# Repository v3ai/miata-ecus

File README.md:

# miata-ecus

A plug-in [rusEFI](https://rusefi.com) engine computer for the 1989–2005 Mazda Miata (NA and NB). It has two parts:

- **One universal daughterboard.** It does all the engine control: an STM32F405 (an STM32F407 up to rev 0.11) running rusEFI, plus an on-board
  LSU 4.9 wideband controller (the open-source FOME/rusEFI design).
- **A motherboard for each model year.** Each one takes the stock harness connector and carries the year-specific
  wiring, the MAP sensor, the wideband sensor plug, the add-on header and USB-C. It goes in the stock ECU's case
  (1990–95; the 1996–2005 fit is unchecked) with three openings cut: the wideband plug, USB-C and the MAP hose.

The daughterboard is a castellated module: it lies flat on the motherboard, its 80 edge pins soldered to two rows of lands.

<table>
<tr>
<td width="50%"></td>
<td width="50%"></td>
</tr>
<tr>
<td align="center"><sub>Daughterboard lifted off its lands</sub></td>
<td align="center"><sub>The universal daughterboard (rev 0.14)</sub></td>
</tr>
</table>

<sub>Renders from the 3D viewer in <a href="viewer/"><code>viewer/</code></a>, with black solder mask (<code>MASK=black</code> in <code>viewer/pcb3d.py</code>). The harness header, the wideband connector, the card socket, the MAP sensor and the heater fuse F1 are simplified stand-in models.</sub>

**Who it is for:** people who want to replace the stock engine computer of a manual-gearbox Miata with a tunable,
open-source one, and can do their own wiring and tuning. It is for off-road and competition use. Automatic cars are untested.

## Start here: pick your year

One page per model-year range, with what to add, where the stock ECU is, the steps in order, the settings and the
first-start checks:

[**1989–93**](quickstart/1989-93.md) · [**1994–95**](quickstart/1994-95.md) · [**1996–97**](quickstart/1996-97.md) ·
[**1999–2000**](quickstart/1999-2000.md) · [**2001–05**](quickstart/2001-05.md)

**Status:** no board has been built or run yet. Every board is fully routed and passes KiCad DRC, and the designs have
been checked on the desk and in simulation ([VERIFICATION.md](VERIFICATION.md)), but no person has reviewed the
schematics. The supported path is an assembled unit until a first board has been built.

| If you want to | Read |
|---|---|
| Build the boards yourself (solder the module, first flash, bench check) | [BUILD.md](BUILD.md) |
| Fit the ECU to a car (labelled pictures, pin maps, MAP hose, wideband, first start) | [INSTALL.md](INSTALL.md) |
| Order the boards and parts | [ORDERING.md](ORDERING.md) |
| See what changed in each revision | [CHANGES.md](CHANGES.md) |

What changed in each revision: [CHANGES.md](CHANGES.md)

## Features and limitations

No board has been built yet. "Can" below means the hardware is designed for it and the firmware is set up for it; where
the firmware part has run in [emulation](firmware/sim/), that is as far as the proof goes.

### What it can do

**On every year**
- **Plugs into the stock harness** and goes in the stock ECU's case (1990–95; the 1996–2005 fit is unchecked) with
  three openings cut.
- **Fuel from manifold pressure** (speed-density), with the MAP sensor on the board. The ECU ignores the stock
  airflow meter's signal.
- **Reads the car's own air-temperature sensor**, with nothing to wire: on 1990–97 it is inside the airflow meter, so
  the meter stays plugged in; on 1999–2005 it is the sensor in the air filter box. Taking the meter out is an option
  with a GM sensor ([INSTALL.md](INSTALL.md#taking-the-airflow-meter-out-optional)).
- **MAP sensor good for boost:** 15–700 kPa absolute, so a turbo or supercharger needs no sensor change.
- **Wideband oxygen sensor controller on the board** for a Bosch LSU 4.9. No separate gauge or controller box. The
  board's connector takes AEM's ready-made X-Series sensor harness (30-3427).
- **Closed-loop fuel from the wideband**, switched on from the first start: ±10 % at idle and cruise, +10 / −5 %
  under load.
- **A base tune for each year**, loaded by the year button in TunerStudio ([what is in it](firmware/README.md#base-tune)).
- **Four injector outputs** for high-impedance injectors. Sequential on 1994–2005; in pairs on 1989–93, as the
  stock harness is wired (two jumpers on that board are for a car with one wire per injector).
- **Four ignition outputs** (5 V logic): two on the harness for the stock coils, two more on the AUX header for one
  coil per cylinder.
- **Closed-loop idle** (on cars with a throttle position sensor), radiator fan, second fan, A/C clutch, fuel pump,
  check-engine light and tachometer, on the stock wires.
- **One USB-C port** for tuning (TunerStudio) and firmware updates, including the wideband's firmware.
- **Logging to a microSD card** in a socket on the daughterboard (rusEFI's own logger).
- **Protected outputs.** Every driver limits its current and shuts down when it overheats. In simulation every
  harness pin was shorted to ground, 14.4 V and 24 V; what still fails is listed in
  [VERIFICATION.md](VERIFICATION.md#rev-08-driver-temperature-and-protected-outputs).

**By year**

| | 1989–93 | 1994–95 | 1996–97 | 1999–2000 | 2001–05 |
|---|---|---|---|---|---|
| Injection | pairs | sequential | sequential | sequential | sequential |
| Variable valve timing | – | – | – | – | closed loop, rusEFI's target table |
| Knock sensor | add your own | add your own | add your own | stock sensor | stock sensor |
| Alternator voltage | alternator's own | alternator's own | alternator's own | ECU, ships off | ECU, ships off |
| Main relay held by the ECU | – | – | – | – | 2003–05 |
| Stock oxygen-sensor heater | – | – | driven | driven | not driven |
| Throttle position | switch only on manual cars | sensor | sensor | sensor | sensor |

**For a turbo and other add-ons** (the 20-pin add-on header, [pin map](INSTALL.md#header-pin-maps))
- Boost-control valve output, already assigned in the firmware, with a fused 12 V for the valve.
- **Flex-fuel sensor input** (GM / Continental type).
- **Nitrous arming input** for rusEFI's nitrous control.
- **CAN bus** for a dash or gauges: the bus the on-board wideband reports on.
- Knock sensor input for the cars that have none.
- Coil 3 and coil 4 outputs.
- A spare 0–5 V analog input, two inputs for magnetic (VR) crank and cam sensors, 5 V and a fused 12 V.
- rusEFI's own functions are all in the firmware (launch control, boost by table or closed loop, knock retard,
  general-purpose PWM tables, Lua scripts). None of them is set up or tested on this board.

### What it can't do

- **It is untested.** No board has been assembled, powered or run in a car.
- **The base tune is a starting point.** The tables came from other people's cars. Nobody has tuned them under
  boost, and the 1989–97 fuel table stops at 128 kPa.
- **No drive-by-wire throttle.** Every supported car has a cable throttle; this only matters for an engine swap.
- **High-impedance injectors only**, and the ignition outputs need coils with built-in igniters or the stock
  igniter. They can't drive a bare coil.
- **One wideband**, four cylinders.
- **The stock case has to be cut:** three openings for the wideband plug, USB-C and the MAP hose, and a way out for
  the add-on ribbon cable if you use that header. The 1996–2005 boards still have the 1990–95 outline and mounting holes.
- **The add-on header is a ribbon-cable header inside the case**, not a sealed plug, and its 12 V pin is fused at
  1.1 A.
- **Sustained high rpm in a hot cabin is the thermal limit**, most of all on 1989–93 cars: see
  [Things to know before ordering](#things-to-know-before-ordering).
- **1990–93:** the fuel pump stays as stock, switched by a contact in the airflow meter (which stays plugged in).
  Manual cars have no throttle position sensor until one is [fitted](#throttle-position-sensor-198993-manual-cars).
- **1999–2005:** alternator control ships switched off until the wire has been checked on a car.
- **Not street legal as an emissions device.** No OBD-II diagnostics or readiness monitors, no immobiliser, and it
  doesn't run the EGR valve, the 1999–2005 purge valve, the 2001–05 intake shutter valves (VTCS) or the rear oxygen
  sensor. The 1999–2000 VICS solenoid is wired but not set up.
- **Automatic cars are untested** (manual cars, and automatics swapped to manual, are the supported ones), and the transmission unit's signals are mostly left unconnected.
- **2004–05 Mazdaspeed is not supported.**

> **Status:** every board is fully routed and passes KiCad DRC (no clearance errors, no unconnected items), and each
> schematic's netlist has been checked pad-by-pad against its board. **None of them has been built or tested yet**, and
> no person has reviewed the schematics. Read each board's README, especially its *Still to verify* or *Before ordering* list.
> Verification (desk and simulation): [VERIFICATION.md](VERIFICATION.md). What changed in each revision, including the
> boards ordered in November 2026: [CHANGES.md](CHANGES.md).

| Board | Folder | Rev | Harness header | Case fit |
|---|---|---|---|---|
| Daughterboard (all years) | [`daughterboard/`](daughterboard/) | 0.14 | 2 × 40 castellated edge pins, soldered to the motherboard | 125 × 70.5 mm, 6 layers |
| 1989–95 (NA6 and NA8; assembled as a 1989–93 or a 1994–95 version) | [`motherboards/1989-95/`](motherboards/1989-95/) | 0.19 | TE 174917-6, 48 pins | stock NA case outline |
| 1996–97 (NA8, OBD-II) | [`motherboards/1996-97/`](motherboards/1996-97/) | 0.15 | TE 178780-1, 76 positions | **provisional** (NA outline) |
| 1999–2000 (NB1) | [`motherboards/1999-2000/`](motherboards/1999-2000/) | 0.15 | TE 178780-1, as 1996–97 (the car's own is the 64-position 176122-6; its plugs are the same housings) | **provisional** (NA outline) |
| 2001–05 (NB2, VVT) | [`motherboards/2001-05/`](motherboards/2001-05/) | 0.15 | TE 353830-5, 72 positions | **provisional** (NA outline) |

Each board folder contains:
- the KiCad 7 project (schematic and board);
- a schematic PDF;
- JLCPCB gerbers, BOM and placement files in `fab/`, with the DRC report, named for the board and revision (for example
  `miata-ecu-motherboard-1989-95-rev0.19_jlcpcb_gerbers.zip`). The JLC BOM is the SMD parts (and USB-C);
  `…_self_order_bom.csv` is everything you order and solder yourself, and
  [`additional-parts/order_all_boards.csv`](additional-parts/order_all_boards.csv) adds up every motherboard, a daughterboard for each and the in-car parts
  (the same list as a page with quantities and tick boxes: [`additional-parts/shopping_list.html`](additional-parts/shopping_list.html));
- renders;
- a README with the pinout, assembly notes and open questions.

## Firmware and flashing
The rusEFI board definition is in [`firmware/`](firmware/): pin map, year presets, and a flasher for the wideband MCU.
GitHub Actions builds it on every push: the firmware, the rusEFI console bundle and the TunerStudio `.ini`. Released
builds go on the *Releases* page (a `fw-v*` tag publishes one); none has been released yet.
See [`firmware/README.md`](firmware/README.md). It compiles, but hasn't run on hardware yet.
- **One USB-C port for everything.** The USB-C on the motherboard's bottom edge goes to the main MCU (STM32F405).
  - **First flash:** ST's DFU mode (hold BOOT, tap RESET).
  - **Later updates:** from the rusEFI console through the OpenBLT bootloader, with no buttons to press.
  - **Tuning:** TunerStudio over the same port. Popular Vehicles picks the model year; the tune is stored in the
    MCU's flash.
- **The wideband MCU (STM32F103) is programmed through the main MCU.** With the engine off, press "Flash on-board
  wideband" in TunerStudio, or type `wbo_uart_flash` in the rusEFI console.
  - The main MCU controls the F103's BOOT0 and reset lines and writes the wideband firmware through the F103's
    built-in ST serial bootloader. The firmware is rusEFI's wideband controller with this board's port
    (`firmware/wideband`), and the main firmware carries it.
  - The SWD Tag-Connect pads on the bottom of the daughterboard (J102) are a fallback.

## Air temperature sensor
The ECU reads the car's own Mazda sensor on its own wires: inside the airflow meter on 1990–97 (so the meter stays
plugged in) and the separate sensor in the air filter box on 1999–2005. The year buttons load its curve from Mazda's
workshop tables, and the firmware accounts for the board's 2.7 kΩ pull-up and divider (2.39 V at −20 °C, 1.41 V at
20 °C, 0.21 V at 100 °C at the processor pin). A car whose airflow meter comes out uses a GM open-element sensor on
the meter's two wires instead and enters its curve in TunerStudio: [INSTALL.md](INSTALL.md#taking-the-airflow-meter-out-optional).

## Throttle position sensor (1989–93 manual cars)
The 1989–93 manual cars have no throttle position sensor: the part on the throttle body is a switch with an idle
contact and a full-throttle contact. The automatics have a real 0–5 V sensor on 2M, as do all 1994–2005 cars. The ECU
calculates fuel from its MAP sensor, so a manual car runs without one, but rusEFI then treats the throttle sensor as
failed: no closed-loop idle, no throttle-based acceleration fuel and no overrun fuel cut.

The switch's plug has three wires: idle contact (1N), ground (2D) and full-throttle contact (2L). A sensor needs
three: 5 V, ground and signal. So, as on rusEFI's Hellen NA6 and MRE boards, a sensor plugs into the stock plug and the
1989–95 motherboard sets those pins with 0 Ω links: **fit R28** (5 V on 1N) and **move R29 to R30** (2L to
the throttle input). The kit, in the board's self-order BOM as "Manual cars":
- **Sensor:** a Kia sensor with the same 3-pin Mazda plug (Kia 0K01118911, or the others the
  [rusEFI wiki](https://wiki.rusefi.com/Legacy-Miata-NA-48-pin-board-for-MRE) lists).
- **Mount:** [Mazda NA6 Miata variable TPS mount](https://www.thingiverse.com/thing:3414132), printed in ASA.
- **Or instead:** [Flyin' Miata's TPS upgrade kit](https://flyinmiata.com/products/tps-upgrade) with its sensor.

Check the plug's wiring and the sensor's pins on your car before fitting R28: see the
[1989–95 README](motherboards/1989-95/README.md). Automatics leave R28 and R30 off.

## Things to know before ordering
- **[ORDERING.md](ORDERING.md)** is the ordering guide for the current boards: what to buy where, board settings at
  JLCPCB, the placement preview, stock and order sequence.
- **Measure one injector's inductance first** (LCR meter, injector unplugged). The heat the injector clamps put into
  the board scales with it, and it is not known for Miata injectors: the design is sized for 20 mH, earlier revisions
  assumed 8 mH. At sustained 7200 rpm with 20 mH injectors the board model puts the processor 32–40 °C above the air
  around the board on 1994–2005 cars and 45–56 °C on stock-wired 1989–93 cars, against a 105 °C junction rating.
  That is the standard grade every other Miata plug-in ECU read uses, and it stays. Numbers:
  [VERIFICATION.md](VERIFICATION.md#board-temperature).
- **1990–93 cars at sustained high rpm.** On the stock paired wiring one driver and one clamp TVS work each pair
  of injectors, as on rusEFI's and Speeduino's boards, and each wire opens once per revolution. For this board that
  is the hottest arrangement: with 20 mH injectors held at 7200 rpm the model keeps that clamp (a 150 °C part) inside
  its rating only up to 33–46 °C around the board, and up to 61–72 °C at 5000 rpm. With 8 mH injectors it is about
  90 °C at 7200 rpm. For track use, set the injection mode to sequential (no rewiring: 78–88 °C at 7200 rpm) or
  convert the car to one wire per injector (about 100 °C). Both are untried:
  [INSTALL.md](INSTALL.md#4-year-specific-steps).
- **The wideband connector has not been tried with a harness.** The motherboards carry a JST PUD header
  (S08B-PUDSS-1) for AEM's X-Series sensor harness 30-3427. AEM's instructions name the harness's terminal, which
  belongs to this connector series, and a photograph of the plug agrees with the board's pin numbering. Each pin's
  wire colour is printed beside the connector: compare a harness with the print before the first use
  ([INSTALL.md](INSTALL.md#header-pin-maps)).
- **Clamp TVS.** The daughterboard's injector clamp TVS is Littelfuse's 1.5SMC16A (2,709 at JLCPCB on 2026-11-15).
  Any SMCJ14A or SMDJ14A fits the same pads if it runs out; the
  [daughterboard README](daughterboard/README.md#before-ordering) names two.
- **1996–2005 case geometry is a placeholder.** These motherboards use the NA board outline and mounting holes until a
  stock 96–97 / NB case is measured. The 76-pin 96–97 header is 130 mm wide and must clear the real case. The
  owner's own pilot of two 1996–97 sets is how that case gets measured ([ORDERING.md](ORDERING.md#5-order-in-this-sequence));
  other 1996–2005 buyers should wait for the result.
- **2001–05 Mazdaspeed:** pin 4R is the second intake-air-temperature sensor on the turbo cars, not the VVT valve.
  Don't fit the 01–05 board to a Mazdaspeed unmodified.
- **Wideband layout is new.** The wideband *circuit* is FOME's proven design. Since daughterboard rev 0.3 its *layout*
  is this board's own, so bring it up and check it against a known sensor before relying on it.
- **MAP sensor:** an MPX5700AP (absolute, single barb), fitted flat with its marking up. The barb's position on the
  footprint was taken from a photo; check it against a real part.

## Repository layout
| Path | What |
|---|---|
| `daughterboard/`, `motherboards/<years>/` | The released boards (see above) |
| `scripts/` | The design source. Every board is generated from Python: parts, netlist, placement, a grid router, schematic generation, release packaging |
| `mb/ecu_mb.pretty/` | Project footprints (harness headers named by OEM terminal, the flat MPX5700AP, USB-C, M4 case hole) |
| `research/` | Pinout research for 1996–2005 (sources compared per pin); the rev 0.10 design audit (every figure the board relies on, its source, and what could not be checked); ST's pin data files |
| `bom/` | Complete BOMs with prices, one CSV per year range: daughterboard, motherboard and the extra parts for the car installation ([how to read them](bom/README.md)) |
| `ordered-boards/2026-11/` | The board set ordered in November 2026 (daughterboard rev 0.9), as ordered |
| `review/2026-11/` | The November 2026 design review: findings, next steps for the next batch, the full report and the working notes ([start here](review/2026-11/README.md)) |
| `viewer/` | Interactive 3D viewer: the daughterboard alone, or assembled on any year's motherboard. Click a part for its details and shop links |
| `firmware/` | The rusEFI board definition, the wideband flasher, the simulation tests and the verification tools. rusEFI itself is a submodule in `firmware/ext/rusefi` |
| `website/` | A black-and-white Shopify theme for selling the boards, draft product listings and product photos ([website/README.md](website/README.md)) |
| `quickstart/` | One page per model-year range: what to add, the steps in order, the settings, the first-start checks |
| `BUILD.md` | Building the boards yourself: soldering the module, the through-hole parts, bench check, first flash |
| `INSTALL.md` | Fitting the ECU to a car: labelled pictures, header pin maps, the MAP hose and wideband per year, first start |
| `CHANGES.md` | What changed in each revision |
| `images/` | Renders, and the labelled pictures and pin maps (`scripts/annotate.py` redraws those from the board files) |
| `ORDERING.md` | The ordering guide for the current boards |
| `VERIFICATION.md` | Pinout, datasheet, simulation, flashing and safety review, with the hardware changes it calls for |
| `.github/workflows/firmware.yaml` | CI: checks the pin map against the board design and builds the firmware |

## Rebuilding
You need:
- **KiCad 7.0** with its Python `pcbnew` module, and `kicad-cli`;
- **Python 3** with `shapely` 2, `numpy`, `scipy`, `Pillow`, `openpyxl` and `matplotlib`;
- **`rsvg-convert`**, for the renders.

```sh
# daughterboard: build, route, finish, then the release folder
LAYERS=6 scripts/daughter_make.sh work/daughter
scripts/daughter_release.sh work/daughter/finished.kicad_pcb out/daughterboard

# a motherboard: <year module> <short name> <rev>, e.g. 1999-2000
scripts/mb_make.sh mb_nb1 9900 0.9      # writes mb/release_9900
```

Routing takes 10–40 minutes per motherboard and about an hour for the daughterboard.

`mk_hdr_fp.py` reads the harness-header geometry from the rusEFI hellen-one boards and KiCad library. Point it at them
with `MIATA_REF` and `RUSEFI_LIBS`. The generated footprints are already in `mb/ecu_mb.pretty/`.

The firmware build is described in [`firmware/README.md`](firmware/README.md).

The viewer is a static page. To open it, run `cd viewer && python3 -m http.server`, then browse to `http://localhost:8000`.
`viewer/pcb3d.py` rebuilds its assets from a board; it also needs `trimesh`, `cascadio`, `Pillow` and `gltfpack`.

The labelled pictures and pin maps in [INSTALL.md](INSTALL.md) come from the viewer and the board files:
`scripts/annotate.py --three <unpacked three@0.160.0 package>` redraws them (needs Playwright with Chromium, and `Pillow`).
`scripts/render_photos.py` renders the pictures at the top of this page and the shop's product photos the same way,
from a black-mask build of the viewer's assets.

### Making a release
After a change to a finished board (or only its revision), regenerate everything derived from it:
1. Set the revision: `REV` in `scripts/design.py` (daughterboard) and `DAUGHTER_REV` in `scripts/annotate.py`; the
   revision text on a motherboard's silkscreen, and a `CHANGES` entry in its year module (`scripts/mb_*.py`).
2. `scripts/reexport.sh daughter`, and for each motherboard
   `scripts/reexport.sh <year module> <short> <rev> <board folder>`, e.g.
   `scripts/reexport.sh mb_na96 9697 0.12 motherboards/1996-97`. It runs the board's checks first and stops on a
   failure, then rewrites the fab files, BOMs, schematics, PDF, DRC report, parts workbook and README. Delete the
   previous revision's fab files.
3. The 3D viewer: `viewer/pcb3d.py <board> "<prefix>" <key>` per board, e.g.
   `viewer/pcb3d.py motherboards/1996-97/miata_mb_9697.kicad_pcb mb9697_ mb:mb_na96` (the daughterboard takes an
   empty prefix and the key `daughter`). Update the revisions in `viewer/index.html`.
4. The pictures: `scripts/annotate.py --three <dir>`, then
   `scripts/render_photos.py --three <dir> --assets <scratch folder> --build`.
5. The order list: `scripts/order_all.py additional-parts/order_all_boards.csv`, and the revisions in
   `additional-parts/shopping_list.html`.
6. Check: `firmware/tools/check_pins.py`, `firmware/tools/check_mcu_pins.py`, `scripts/check_lcsc.py` and
   `firmware/tools/board_checks.py --brief`.

The costed BOMs (`*_costed_bom.csv`) and the per-year BOMs in `bom/` are generated from a price snapshot outside this
repository; regenerate them after a release so their file names and lines follow the boards.

## Credits and licences
- This project (the board designs, scripts and viewer) is released under the [MIT licence](LICENSE).
- One firmware file is GPL-3.0: `firmware/board/miata_nb_tune.cpp` holds the 1999–2005 base tune tables, copied from
  rusEFI. The firmware you build includes rusEFI, so the built firmware is GPL-3.0 as a whole
  ([firmware/README.md](firmware/README.md#licences)).
- The wideband controller circuit is the FOME / rusEFI open-source wideband module
  ([mck1117/wideband](https://github.com/mck1117/wideband), `board_module` rev C, MIT licence). Its source files and
  licence are in `scripts/wideband_ref/`.
- The circuit topologies follow rusEFI's hellen-one modules, and the harness pinouts were cross-checked against the
  rusEFI hellen Miata boards and the Mazda workshop manuals (see `research/`).

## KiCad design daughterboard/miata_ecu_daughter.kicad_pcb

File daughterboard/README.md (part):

# Miata ECU — daughterboard rev 0.14 (routed, unverified)

125 × 70.5 mm, **6 layers**, a **castellated module**. All parts are on top. J1 (top edge: power and outputs) and
J2 (bottom edge: inputs, comms and the LSU 4.9 wideband sensor) are rows of 40 plated half-holes along the long edges,
2.54 mm apart. The module lies flat on the year-specific motherboard and is soldered to its lands JD1 / JD2, by
reflow or with an iron: no connectors, standoffs or screws.

## What changed in rev 0.14
Silkscreen only: same copper, parts, placement and pinout as rev 0.13.
- **The status lights are named:** RUN (D1, green), COMM (D2, blue), WARN (D3, yellow), ERR (D4, red) and PWR (D5,
  green, the 3.3 V supply), each under its light, and so are the buttons, BOOT (SW1) and RESET (SW2); their
  references are on the assembly drawing (F.Fab).
- **No silkscreen on a pad, a part, other silkscreen or the board edge** (it had 404 such items, 125 of them KiCad
  silkscreen overlaps and 72 silkscreen on copper): references moved beside their parts, the rest to F.Fab, part
  outlines cut back where they met pads, other parts or text, and pin-1 marks on a pad moved to F.Fab
  (`scripts/daughter_rev14.sh`, `scripts/silk_clean.py`; the release check now fails a board with any). J4's
  reference, printed upside down, is upright.

## What changed in rev 0.13
- **Castellated edges instead of pin headers.** The long edges were cut through the centres of the J1 / J2 pin rows,
  so the 80 plated header holes (1.0 mm) are now plated half-holes on the edge, and the board is 125 × 70.5 mm
  (was 125 × 76). Each castellation's pad, on the top and bottom copper, is 1.6 mm along the edge and reaches 1.3 mm in
  from it; seven (J1-16, J2-6, -7, -8, -14, -15, -25) reach 0.85 mm, where a part or track sits close inside.
- **No headers, standoffs or mounting holes:** J1 / J2 were 1×40 male headers (C2977586) on the bottom, plugged into
  8.5 mm sockets on four M3 × 11 mm standoffs; H1-H4 were in the strips the cut removed. The module now sits about
  0.1 mm above the motherboard, on its solder joints.
- **Same parts, placement and routing as rev 0.12;** the JLC BOM and placement file are identical. The cut removed the
  40 GND stitching vias along the old edges, and 15 track ends that entered the pins were pulled in to keep 0.3 mm
  from the new edge (`scripts/castellate_daughter.sh`: `castellate_daughter.py`, `castellate_copper.py`,
  `backport_copper.py`). KiCad DRC: no errors, nothing unconnected; `jlc_fab_check.py` checks JLCPCB's castellation
  rules (0.6 mm drill, 0.6 mm between holes, 0.25 mm ring).
- **J102** (the wideband controller's SWD pads) stays on the bottom, so it can be reached only before the module is
  soldered down. It is a fallback: the wideband controller is programmed through the main processor and its ROM
  bootloader (rev 0.4 on). J3, the main processor's SWD pads, is on top.
- **Order with castellated holes** ([ORDERING.md](../ORDERING.md)). Rev 0.13 goes with motherboard rev 0.16 or later (1989-95)
  or 0.12 or later (1996-2005), which have the lands. It does not fit the earlier, socketed motherboards, and an earlier
  daughterboard does not fit these.
- **Temperature:** the board model now includes the motherboard under the module (`board_thermal.py --flat`). The
  module runs 1-5 °C warmer than the old free-air figure, and the 9-13 °C the header pins were estimated to take away
  are gone: at sustained 7200 rpm, the processor is +43 °C on sequential cars and the hottest clamp TVS +119 °C on a
  stock-wired 1989-93 car in batch mode (+74 °C in sequential mode). Figures and limits:
  [VERIFICATION.md](../VERIFICATION.md#board-temperature). Unmeasured.

## What changed in rev 0.12
- **Processor STM32F405VGT6** (C56621) instead of the STM32F407VGT6, for JLCPCB stock: the same die and datasheet
  without Ethernet and the camera port, neither used here. The rusEFI build is unchanged; the pin map is checked against
  ST's pin data for the F405 and for the F407 and F427, which fit the same pads (`firmware/tools/check_mcu_pins.py`).
- **CAN transceivers U10 / U106: NXP TJA1042T/3** (C132227) instead of the TCAN1042, pin for pin.
- Same routing, placement, outline and pinout as rev 0.11. Rev 0.12 went with motherboard rev 0.15 (1989-95) or 0.11
  (1996-2005); it fits the socketed motherboards from rev 0.13 / 0.9 on.

## What changed in rev 0.11
- **No via in or within 0.1 mm of any SMD pad.** The 200 vias that sat in the eight driver tab pads are now in the
  tabs' drain copper around the pads, and the other in-pad vias moved beside their pads with stubs as wide as the
  track they continue (`scripts/via_out_of_pad.py`, then `scripts/via_ripup.py` and `scripts/finish_route.py` where a
  via had no free spot). No filled vias are needed. `scripts/jlc_fab_check.py` now fails a release with a via in a pad.
- **R110 is 62 Ω (C17971),** not the 0.62 Ω part (C25341) that rev 0.9 and rev 0.10 list.
- Otherwise the same board as rev 0.10: same parts, placement, outline and pinout. Rev 0.11 goes with motherboard
  rev 0.14 (1989-95) or 0.10 (1996-2005).
- The change list behind this revision: [review/2026-11/NEXT-REV.md](../review/2026-11/NEXT-REV.md).

## What changed in rev 0.10
Same outline, same J1/J2 pinout except J2-24 / J2-25; **six layers** instead of four. A rev 0.10 daughterboard goes
with motherboard rev 0.13 (1989-95) or 0.9 (1996-2005); it also fits the earlier motherboards, without the new
inputs. Background and numbers: `VERIFICATION.md`, [Rev 0.10](../VERIFICATION.md#rev-010-six-layers-injector-clamps-card-socket-two-more-inputs-2026-11-13),
and the audit in `research/rev0.10_design_audit.md`.
- **Injector clamp per injector** (D42-D45 ES1D, D46-D49 1.5SMC16A): a fast diode from each injector driver's drain to
  a 16 V TVS that returns to the battery input. The turn-off energy goes there instead of through the driver's own
  clamp: 8.8 mJ per shot instead of 15.3 mJ with 20 mH injectors, peak 32 V instead of 43 V. The injector current
  takes about 0.16 ms longer to fall, so **check the injector dead time in the tune**. The TVS is Littelfuse's
  1.5SMC16A since 2026-11-15 (15.2-16.8 V, 150 °C junction): Vishay's TPSMC16A, the same voltages with a 185 °C
  junction, was named first but JLCPCB had none, nor any other part of this package rated above 150 °C. What that
  means for 1989-93 cars is under [Before ordering](#before-ordering), item 8.
- **1989-93 cars: one driver per injector wire** (2026-11-15, no board change). On the stock harness INJ1 and INJ2
  each work a wire with two injectors; INJ3 and INJ4 are not connected on the motherboard (its links R38 / R39 not
  fitted; up to rev 0.18, no shunts on JP1 and JP2). Before, a second driver sat in parallel on each wire.
- **220 Ω in series with each low-side driver input** (R152-R159): ST's VND7NV04 rating asks for at least 150 Ω.
- **microSD socket** J4 (Molex 47219-2001, hinged lid) on SPI2 with 47 kΩ pull-ups on every line but the clock.
  Rated -20 to +85 °C.
- **Two more inputs on J2-24 and J2-25** (a spare UART up to rev 0.9): flex-fuel sensor frequency (PC6, 10 µs filter)
  and nitrous arm (PC7, 100 µs filter), each through 10 kΩ and clamped to 3.3 V. The motherboard adds the sensor's
  pull-up and the switch's pull-down.
- **Check-engine lamp** driven from its processor pin directly (R160), outside the shared driver enable, so the
  firmware can light it on a fatal error.
- **Battery voltage** sensed at the battery input itself (was after the reverse diode and fuse, 0.3-0.4 V low).
- **Logic supply:** fuse F1 1.1 A hold (was 0.5 A), inductor L1 2.2 µH 7 A moulded, 100 nF (C71) at the buck
  converter's input pins.
- **Six layers:** F.Cu, ground plane, two inner signal layers, +3V3 plane, B.Cu. Every rev 0.9 part keeps its place
  except U14, F1, L1, the LED column (1.5 mm lower), the debug pads J3 and the two input clamps D36/D37 with their
  resistors. Inner copper is 15 µm against 35 µm outside, so the injector, valve, logic-supply and USB-supply nets
  stay on the outer layers; `scripts/track_current.py` checks every current-carrying track against its layer.
- **Heat:** each clamp TVS stands under its driver on its own copper column on all four signal layers (about
  176-196 mm² effective). A model of the whole board (`firmware/tools/board_thermal.py`) puts the board 23-31 °C
  above the air around it at sustained 7200 rpm with 20 mH injectors, the injector drivers 30-41 °C, the clamp TVSs
  43-52 °C and the processor 32-40 °C (sequential; 1989-93 cars run warmer, see `VERIFICATION.md`).
- **Routed from scratch** (`scripts/daughter_make.sh`): `route.py` in six-layer mode, then the new exact-geometry
  finisher `scripts/finish_route.py` for the connections and plane vias the grid router left. DRC: 0 unconnected,
  0 clearance errors.

## What changed in rev 0.9
Layout only; the circuit is rev 0.8's.
- **J1 back on the top edge, J2 on the bottom edge**, as up to rev 0.7, with the four mounting holes in the corners.
  The 16 mm strip of output drivers that rev 0.8 put above J1 now sits just below it: each VND7NV04 (Q1-Q8) stands
  with its tab up against its own J1 pin and its leads facing the level shifters, and the relay switches, the
  ignition diodes and pull-down switches and their resistors are mirrored the same way. Everything else keeps its
  rev 0.8 place and copper.
- **Drain copper** per driver: 84-100 mm² on F.Cu and 95-108 mm² on each of In2.Cu and B.Cu (the column now runs from the board edge down past the driver's leads), joined by 34-42 thermal vias (most in the tab pad; order them filled and
  capped). Estimated junction to ambient 48 °C/W, as in rev 0.8 (sequential injectors at 90 % duty, 7200 rpm, 85 °C ambient: 109 °C).
- **On the motherboards** the daughterboard sits 16 mm lower, centred top to bottom (42 mm from the top edge, as up to
  rev 0.7): JD1 and the upper standoffs are at their rev 0.7 places, JD2, the lower standoffs and the AUX header 16 mm
  lower. A rev 0.9 daughterboard needs a motherboard of rev 0.9 or later (1989-95; 1989-93 is now rev 0.11) or 0.7 (1996-2005).
- **Re-routed incrementally:** the rev 0.8 copper was kept everywhere except the nets of the moved parts
  (`route_eco.py`), which `route.py` routed again; four connections were finished by hand (`hand_route_all.py`).
  DRC: 0 unconnected, 0 clearance errors.

## What changed in rev 0.8
Fixes for what the rev 0.7 checks still flagged (`VERIFICATION.md`, [Rev 0.8](../VERIFICATION.md#rev-08-driver-temperature-and-protected-outputs)):
driver temperature, unprotected relay and ignition outputs, the sensor 5 V, the LSU drive wires, the CAN transceivers
and the AUX UART. Existing designators are unchanged where the part stays; new parts have new numbers.
- **Board 16 mm taller (125 × 76 mm).** The new strip along the top edge, above J1, sits over free motherboard space
  on every year (nothing on any motherboard is under it). J1, J2 and the four holes keep their places relative to each
  other, so the motherboards' sockets and standoffs don't move.
- **Low-side drivers Q1-Q8: ST VND7NV04** (DPAK, C155605) instead of the NCV8406A (SOT-223): 60 mΩ instead of 90-210,
  a 200 mJ clamp rating and 2.1 °C/W junction to case. They stand in the new strip, each with its tab down onto its
  own J1 pin, on a column of drain copper on F.Cu, In2.Cu and B.Cu (about 300 mm² per driver over the three layers)
  joined by 28-34 thermal vias, most of them inside the tab pad (`scripts/tab_copper.py`). Estimated junction to
  ambient 48 °C/W (rev 0.7: 109). Sequential injectors at 90 % duty, 7200 rpm, worst-case Rds(on): 84 °C at 60 °C
  ambient, 110 °C at 85 °C (rev 0.7: thermal shutdown). This is the "heat sink": copper and vias, no bolt-on part,
  since the board sits flat in the stock case. **Order the board with the vias epoxy-filled and capped** (JLC's
  via-in-pad process) so solder doesn't wick away from the tabs.
- **Relay, lamp and tach outputs: seven ZXMS6004FF protected low sides** (Q9-Q15, Diodes IntelliFET: current limit,
  thermal shutdown, 60 V clamp) instead of the ULN2003, driven at 5 V by a second SN74LVC4245A (U12) on the same
  enable as the other drivers, with 10k pull-downs (RN2, RN3). A relay or lamp wire shorted to battery now limits
  instead of burning a ULN channel.
- **Ignition outputs protected:** each TC4427 channel sources through its 100 Ω (now 1206) and a B5819W Schottky
  (D31-D34), and a ZXMS6004FF (Q16-Q19, gates from a 74HCT04, U13) pulls the output low. A coil wire shorted to battery
  just reverse-biases the Schottky. R144-R147 (3.3k, 1206) give the spark edge a defined fall with the pull-down off;
  3.3k keeps them inside their rating with a coil wire held at 24 V.
- **Protected harness 5 V:** a second TLS115 (U14) tracking +5V, out on J1 pin 13 (was a ground pin) to the harness's
  sensor 5 V cavities and the AUX header. The first TLS115 now feeds only the MAP sensor on the motherboard, so a
  sensor 5 V wire shorted to battery no longer takes the MAP reading or back-feeds the board. CLT/IAT bias from it;
  the hall pull-ups from it through a common-anode Schottky pair (D35), so a crank or cam wire shorted to battery
  puts nothing into its pull-up.
- **+3V3 shunt clamp:** a TL431 (U15) at 3.56 V drives a BCP53 PNP (Q20) that sinks fault current pushed into +3V3
  through the input clamps, with 2 × 100 µF bulk (C63, C68). Simulated with 1 A pushed in: 3.93 V peak for the first
  microseconds, then 3.56 V (the MCUs' absolute maximum is 4.0 V).
- **LSU drive wires:** F2 (0.1 A PTC) in the VM wire, Schottky clamps from the pump (D40) and virtual-ground (D41)
  drive nodes to +3V3, R108-R110 in 1206 and R137 22k. A short of IP, RT or VM to battery no longer reaches U101's
  outputs or the F103; the 1206 resistors take the short while it lasts (check or replace them after one).
  Firmware: VM_RESISTOR_VALUE 11.6 Ω (R109 + F2).
- **CAN: TI TCAN1042V-Q1** (U10, U106) instead of the SN65HVD230: ±58 V bus fault protection and −40 to 125 °C.
  Supplied from +5V (C67, C122), with 3.3 V I/O.
- **AUX UART:** 10k series resistors (R139, R140) and BAT54S clamps (D36, D37) on PC6/PC7.
- **Battery and ignition sense:** BAT54WS clamps D38/D39 on the dividers' ADC nodes.
- **Switch inputs: 22k/10k dividers** (was 33k): a 12 V signal at 9 V cranking now gives 2.81 V at the MCU, above ST's
  tested 2.31 V threshold. The hall series resistors R61/R63 are 0603.
- **Status LEDs:** comms and warning moved from PD13/PD14 to PC8/PC9 (PD12 run and PD15 error unchanged); the four
  adjacent PD pins left no way out for the fourth LED line. The board firmware is updated to match.
- **Re-routed incrementally** from the rev 0.7 copper (the old layout moved down 16 mm, `scripts/route_eco.py`), then
  `route.py`'s finish passes. The last connections around the wideband MCU and the LED lines were routed by hand
  (`scripts/hand_route.py`, chained by `hand_route_all.py`; a few short nets ripped up and rerouted in a better order),
  and `scripts/clean_dangling.py` removed the stubs that left. DRC: 0 unconnected, 0 clearance errors.

## What changed in rev 0.7
Fixes for the findings of the 2026-11-02 expanded circuit simulation and fault checks (`VERIFICATION.md`, findings
N1-N9). Existing designators are unchanged; new parts have new numbers.
- **U4 is an ST LDL1117S33R** (low dropout, same SOT-223 pinout) instead of the AMS1117-3.3. With about 1 V of dropout,
  the AMS1117 let the wideband MCU's VDDA (REF3033) run up to 0.95 V above its VDD while +5V rose or fell (power-up,
  key-off, crank dips; ST allows 0.3 V). The new part also keeps +3V3 up through an ISO 16750-2 level II crank, and
  is rated from -40 C.
- **D30 (BAT54WS) from the wideband MCU's VDDA to +3V3.** The low-dropout regulator alone still let VDDA lead VDD by
  about 0.8 V at key-off and in a slow brown-out, when the REF3033 holds up longer than +3V3; the Schottky caps the
  difference at about 0.25 V in every case simulated.
- **Clamps on the eight analog inputs:** D19-D26 (BAT54WS Schottky) from each AN_ node to +3V3, after the 5.6k. A
  sensor wire shorted to battery put 9.2 V on its MCU pin; now about 3.55 V, with 1.9 mA into +3V3 instead of the
  MCU. The 5.6k series and the CLT/IAT 2.7k bias resistors are now 0603. A Schottky leaks a little into the input
  when the sensor reads near 0 V, more when hot: estimated 5 mV at the sensor at 60 °C (up to about 46 mV with a
  worst-case part). Compare TPS and CLT readings with a meter on a hot day.
- **Clamps on the three 12 V switch inputs:** D27-D29 (1N4148WS) to +3V3, as on the hall inputs (a battery-fed switch
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
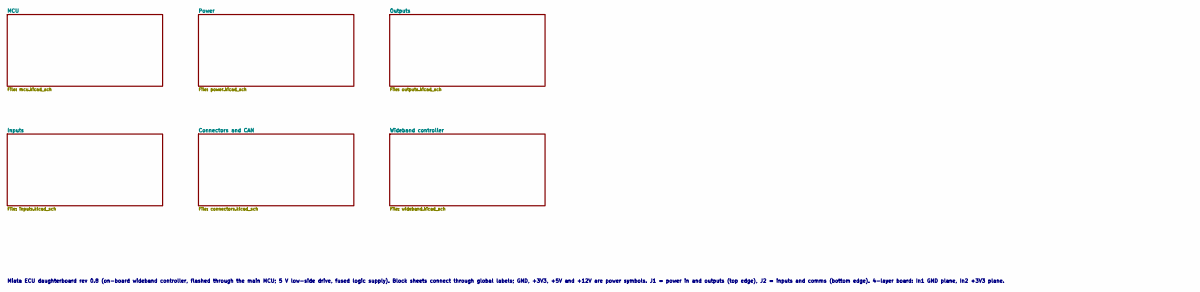
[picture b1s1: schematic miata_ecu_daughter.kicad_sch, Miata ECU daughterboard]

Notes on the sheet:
Miata ECU daughterboard rev 0.8 (on-board wideband controller, flashed through the main MCU; 5 V low-side drive, fused logic supply). Block sheets connect through global labels; GND, +3V3, +5V and +12V are power symbols. J1 = power in and outputs (top edge), J2 = inputs and comms (bottom edge). 4-l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

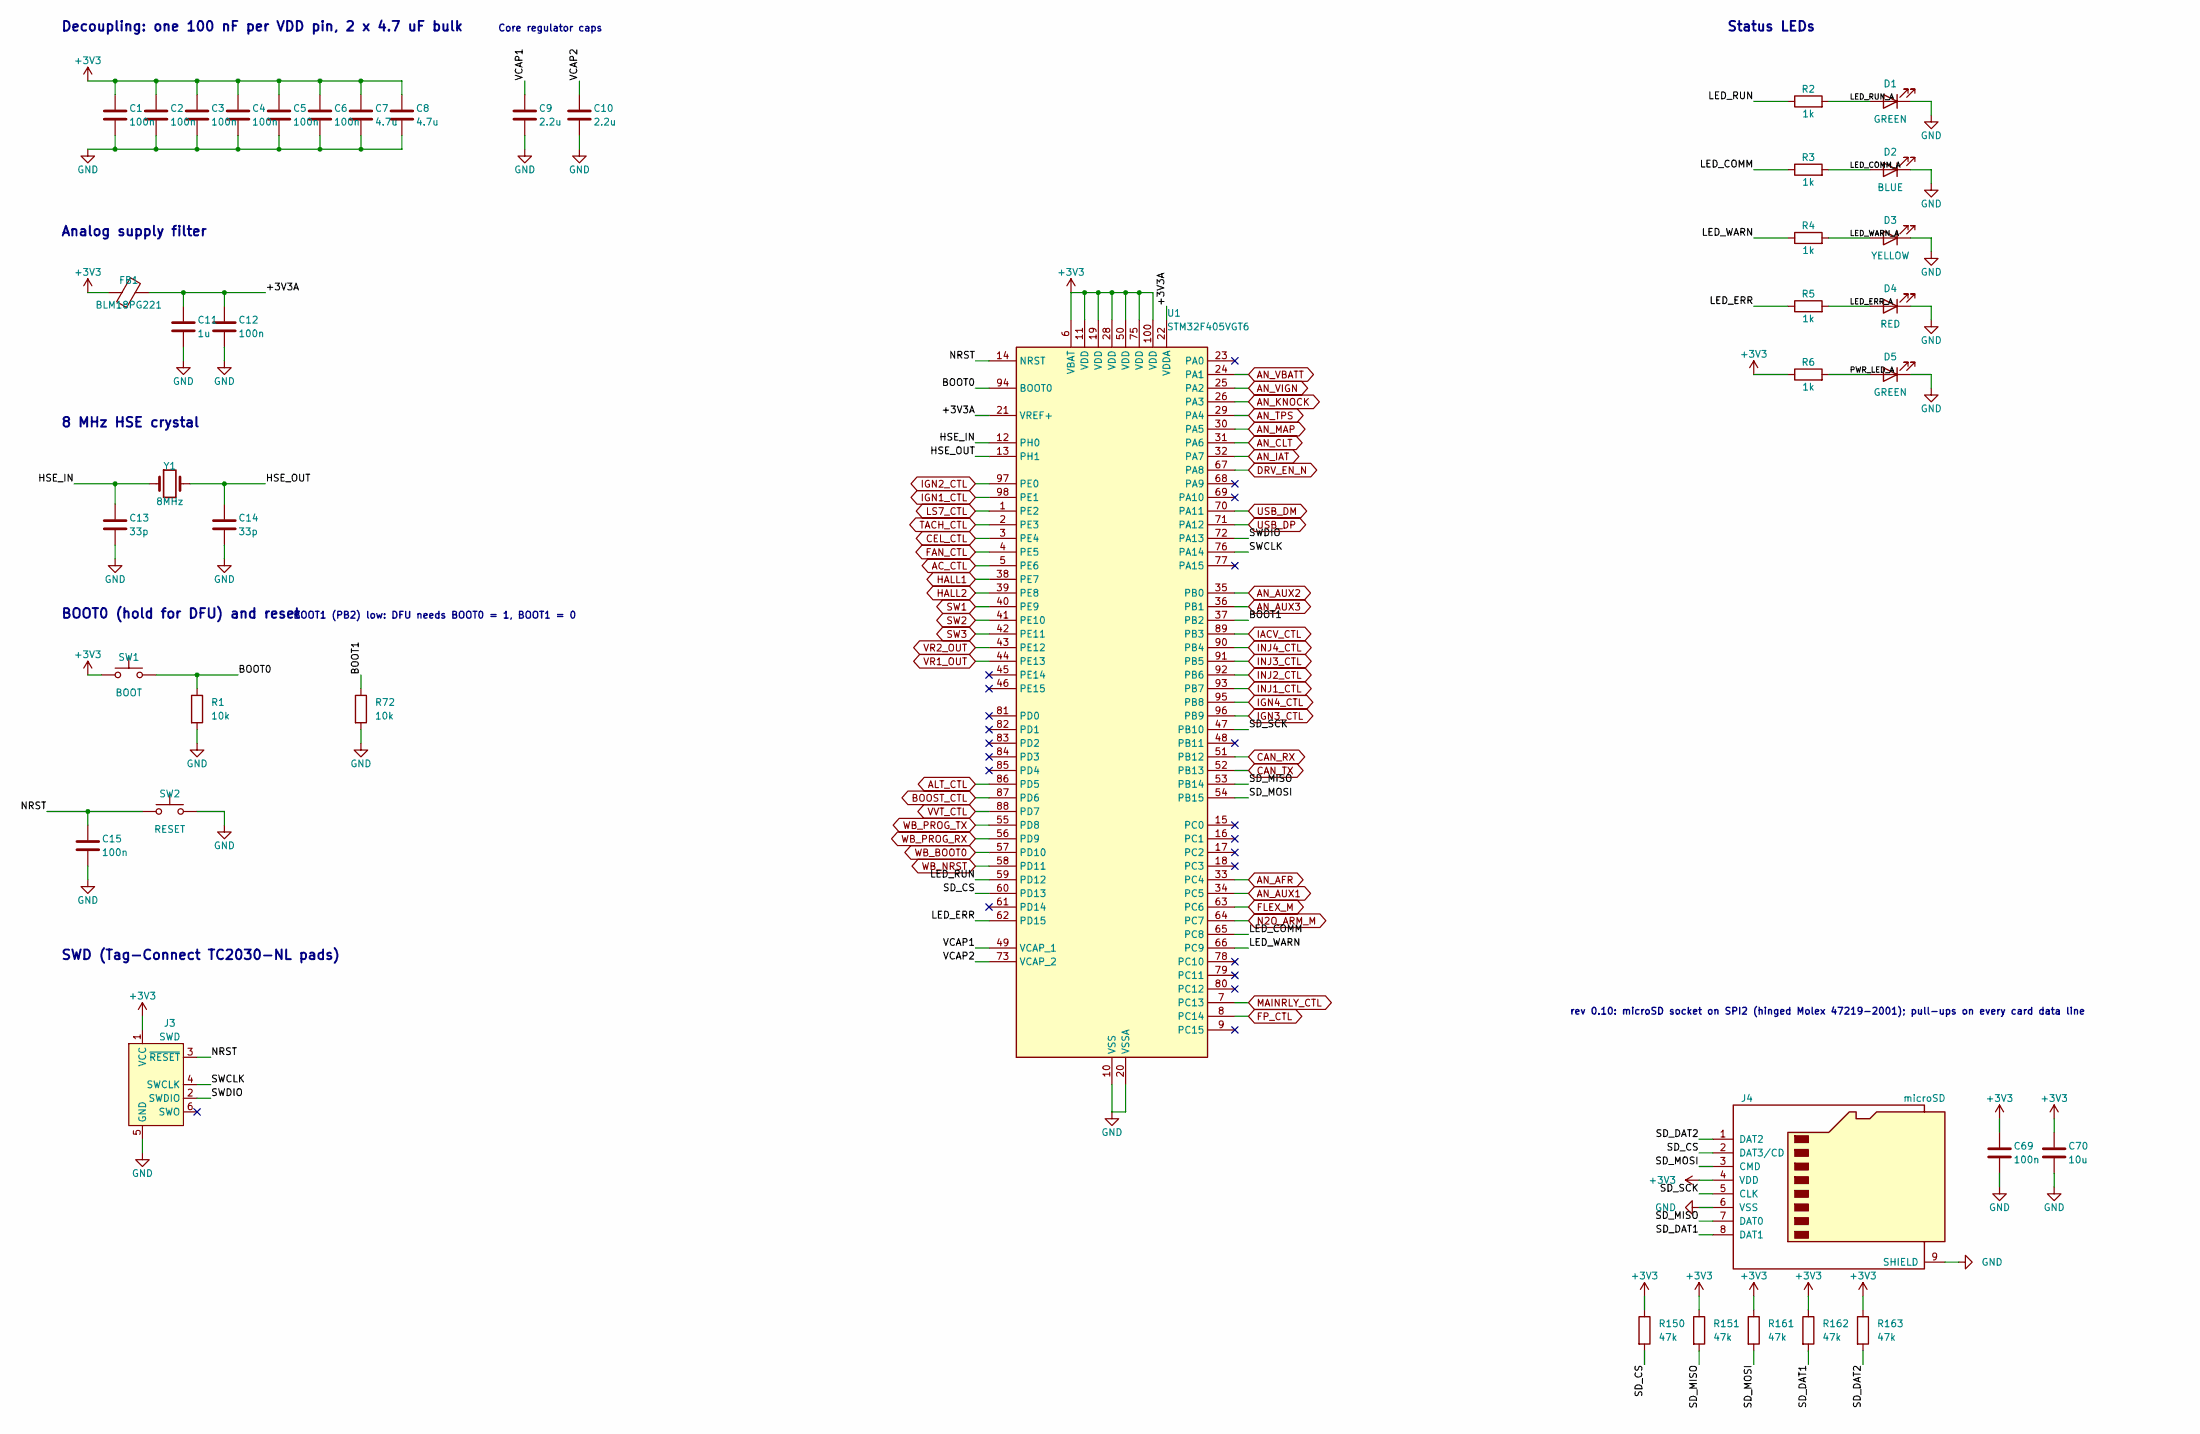
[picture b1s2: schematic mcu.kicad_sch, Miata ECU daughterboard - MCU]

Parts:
C1, C2, C3, C5, C6, C12, C15: 100n; C_0603_1608Metric; LCSC C14663
C4, C69: 100n; C_0402_1005Metric; LCSC C1525
C7, C8: 4.7u; C_0603_1608Metric; LCSC C19666
C9, C10: 2.2u; C_0603_1608Metric; LCSC C23630
C11: 1u; C_0603_1608Metric; LCSC C15849
C13, C14: 33p; C_0603_1608Metric; LCSC C1663
C70: 10u; C_0805_2012Metric; LCSC C15850
D1, D5: GREEN; LED_0603_1608Metric; LCSC C12624
D2: BLUE; LED_0603_1608Metric; LCSC C2288
D3: YELLOW; LED_0603_1608Metric; LCSC C2287
D4: RED; LED_0603_1608Metric; LCSC C2286
FB1: BLM18PG221; L_0603_1608Metric; LCSC C80165
J3: SWD; Tag-Connect_TC2030-IDC-NL_2x03_P1.27mm_Vertical
J4: microSD; microSD_HC_Molex_47219-2001; LCSC C164170
R1: 10k; R_0603_1608Metric; LCSC C25804
R2, R3, R4, R5, R6: 1k; R_0603_1608Metric; LCSC C21190
R72: 10k; R_0402_1005Metric; LCSC C25744
R150, R151, R161, R162, R163: 47k; R_0402_1005Metric; LCSC C25792
SW1: BOOT; SW_Push_1P1T_XKB_TS-1187A; LCSC C318884
SW2: RESET; SW_Push_1P1T_XKB_TS-1187A; LCSC C318884
U1: STM32F405VGT6; LQFP-100_14x14mm_P0.5mm; LCSC C56621
Y1: 8MHz; Crystal_SMD_5032-2Pin_5.0x3.2mm; LCSC C115962

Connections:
+3V3: C1.1, C2.1, C3.1, C4.1, C5.1, C6.1, C7.1, C8.1, C69.1, C70.1, FB1.1, J3.1 (VCC), J4.4 (VDD), R6.1, R150.1, R151.1, R161.1, R162.1, R163.1, SW1.1, U1.6 (VBAT), U1.11 (VDD), U1.19 (VDD), U1.28 (VDD), U1.50 (VDD), U1.75 (VDD), U1.100 (VDD); also elsewhere on the board
/MCU/+3V3A: C11.1, C12.1, FB1.2, U1.21 (VREF+), U1.22 (VDDA)
/MCU/BOOT0: R1.1, SW1.2, U1.94 (BOOT0)
/MCU/BOOT1: R72.1, U1.37 (PB2)
/MCU/HSE_IN: C13.1, U1.12 (PH0), Y1.1
/MCU/HSE_OUT: C14.1, U1.13 (PH1), Y1.2
/MCU/LED_COMM: R3.1, U1.65 (PC8)
/MCU/LED_COMM_A: D2.2 (A), R3.2
/MCU/LED_ERR: R5.1, U1.62 (PD15)
/MCU/LED_ERR_A: D4.2 (A), R5.2
/MCU/LED_RUN: R2.1, U1.59 (PD12)
/MCU/LED_RUN_A: D1.2 (A), R2.2
/MCU/LED_WARN: R4.1, U1.66 (PC9)
/MCU/LED_WARN_A: D3.2 (A), R4.2
/MCU/NRST: C15.1, J3.3 (~RESET), SW2.1, U1.14 (NRST)
/MCU/PWR_LED_A: D5.2 (A), R6.2
/MCU/SD_CS: J4.2 (DAT3/CD), R150.2, U1.60 (PD13)
/MCU/SD_DAT1: J4.8 (DAT1), R162.2
/MCU/SD_DAT2: J4.1 (DAT2), R163.2
/MCU/SD_MISO: J4.7 (DAT0), R151.2, U1.53 (PB14)
/MCU/SD_MOSI: J4.3 (CMD), R161.2, U1.54 (PB15)
/MCU/SD_SCK: J4.5 (CLK), U1.47 (PB10)
/MCU/SWCLK: J3.4 (SWCLK), U1.76 (PA14)
/MCU/SWDIO: J3.2 (SWDIO), U1.72 (PA13)
/MCU/VCAP1: C9.1, U1.49 (VCAP_1)
/MCU/VCAP2: C10.1, U1.73 (VCAP_2)
AC_CTL: U1.5 (PE6); also elsewhere on the board
ALT_CTL: U1.86 (PD5); also elsewhere on the board
AN_AFR: U1.33 (PC4); also elsewhere on the board
AN_AUX1: U1.34 (PC5); also elsewhere on the board
AN_AUX2: U1.35 (PB0); also elsewhere on the board
AN_AUX3: U1.36 (PB1); also elsewhere on the board
AN_CLT: U1.31 (PA6); also elsewhere on the board
AN_IAT: U1.32 (PA7); also elsewhere on the board
AN_KNOCK: U1.26 (PA3); also elsewhere on the board
AN_MAP: U1.30 (PA5); also elsewhere on the board
AN_TPS: U1.29 (PA4); also elsewhere on the board
AN_VBATT: U1.24 (PA1); also elsewhere on the board
AN_VIGN: U1.25 (PA2); also elsewhere on the board
BOOST_CTL: U1.87 (PD6); also elsewhere on the board
CAN_RX: U1.51 (PB12); also elsewhere on the board
CAN_TX: U1.52 (PB13); also elsewhere on the board
CEL_CTL: U1.3 (PE4); also elsewhere on the board
DRV_EN_N: U1.67 (PA8); also elsewhere on the board
FAN_CTL: U1.4 (PE5); also elsewhere on the board
FLEX_M: U1.63 (PC6); also elsewhere on the board
FP_CTL: U1.8 (PC14); also elsewhere on the board
GND: C1.2, C2.2, C3.2, C4.2, C5.2, C6.2, C7.2, C8.2, C9.2, C10.2, C11.2, C12.2, C13.2, C14.2, C15.2, C69.2, C70.2, D1.1 (K), D2.1 (K), D3.1 (K), D4.1 (K), D5.1 (K), J3.5 (GND), J4.6 (VSS), J4.9 (SHIELD), R1.2, R72.2, SW2.2, U1.10 (VSS), U1.20 (VSSA), U1.27 (VSS), U1.74 (VSS), U1.99 (VSS); also elsewhere on the board
HALL1: U1.38 (PE7); also elsewhere on the board
HALL2: U1.39 (PE8); also elsewhere on the board
IACV_CTL: U1.89 (PB3); also elsewhere on the board
IGN1_CTL: U1.98 (PE1); also elsewhere on the board
IGN2_CTL: U1.97 (PE0); also elsewhere on the board
IGN3_CTL: U1.96 (PB9); also elsewhere on the board
IGN4_CTL: U1.95 (PB8); also elsewhere on the board
INJ1_CTL: U1.93 (PB7); also elsewhere on the board
INJ2_CTL: U1.92 (PB6); also elsewhere on the board
INJ3_CTL: U1.91 (PB5); also elsewhere on the board
INJ4_CTL: U1.90 (PB4); also elsewhere on the board
LS7_CTL: U1.1 (PE2); also elsewhere on the board
MAINRLY_CTL: U1.7 (PC13); also elsewhere on the board
N2O_ARM_M: U1.64 (PC7); also elsewhere on the board
SW1: U1.40 (PE9); also elsewhere on the board
SW2: U1.41 (PE10); also elsewhere on the board
SW3: U1.42 (PE11); also elsewhere on the board
TACH_CTL: U1.2 (PE3); also elsewhere on the board
USB_DM: U1.70 (PA11); also elsewhere on the board
USB_DP: U1.71 (PA12); also elsewhere on the board
VR1_OUT: U1.44 (PE13); also elsewhere on the board
VR2_OUT: U1.43 (PE12); also elsewhere on the board
VVT_CTL: U1.88 (PD7); also elsewhere on the board
WB_BOOT0: U1.57 (PD10); also elsewhere on the board
WB_NRST: U1.58 (PD11); also elsewhere on the board
WB_PROG_RX: U1.56 (PD9); also elsewhere on the board
WB_PROG_TX: U1.55 (PD8); also elsewhere on the board

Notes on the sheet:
Decoupling: one 100 nF per VDD pin, 2 x 4.7 uF bulk
Core regulator caps
Analog supply filter
8 MHz HSE crystal
BOOT0 (hold for DFU) and reset
BOOT1 (PB2) low: DFU needs BOOT0 = 1, BOOT1 = 0
SWD (Tag-Connect TC2030-NL pads)
rev 0.10: microSD socket on SPI2 (hinged Molex 47219-2001); pull-ups on every card data line
Status LEDs

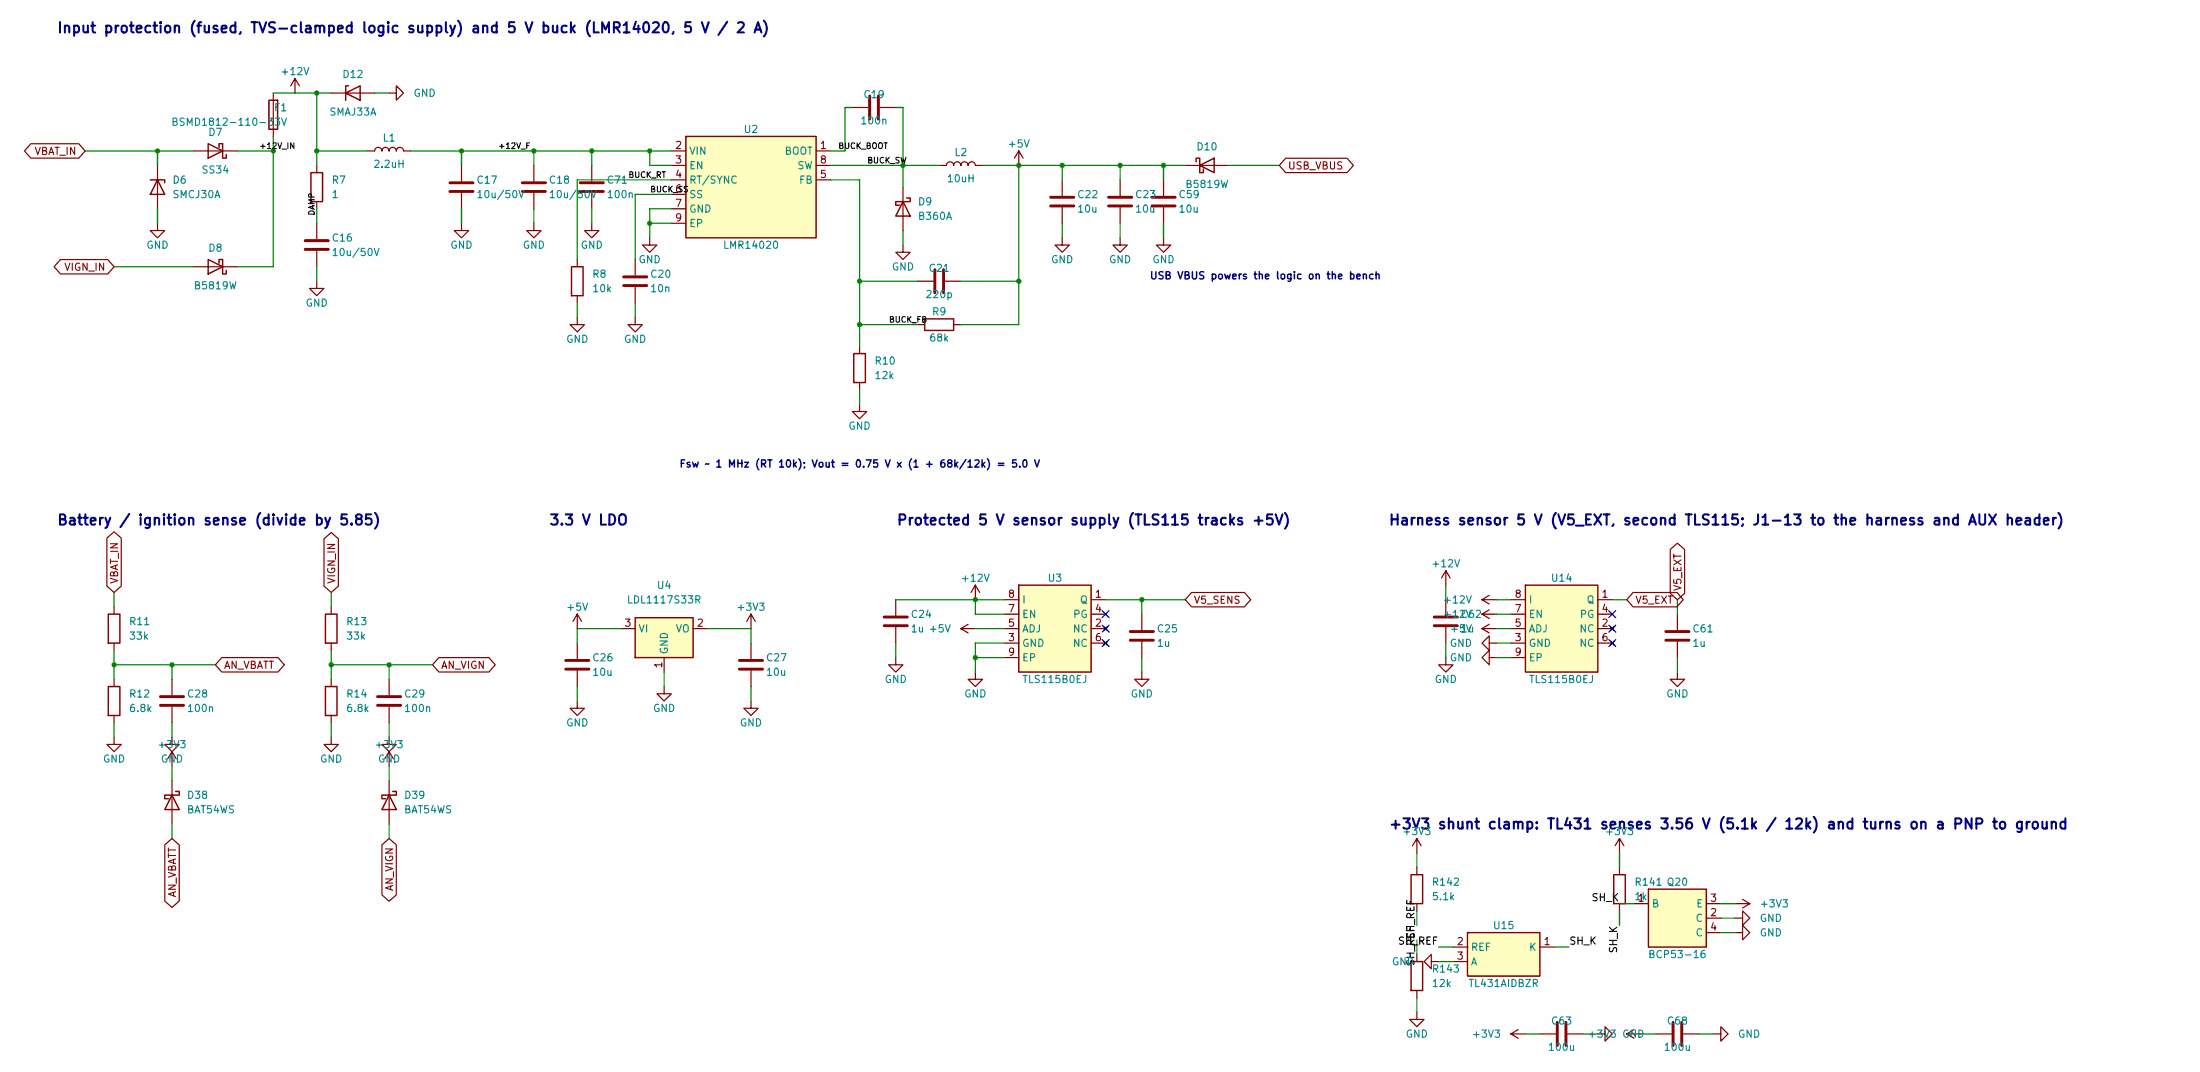
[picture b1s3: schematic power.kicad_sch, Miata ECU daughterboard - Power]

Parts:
C16, C17, C18: 10u/50V; C_1206_3216Metric; LCSC C13585
C19, C71: 100n; C_0603_1608Metric; LCSC C14663
C20: 10n; C_0603_1608Metric; LCSC C57112
C21: 220p; C_0603_1608Metric; LCSC C1603
C22, C23, C26, C27, C59: 10u; C_0805_2012Metric; LCSC C15850
C24, C25, C61, C62: 1u; C_0603_1608Metric; LCSC C15849
C28, C29: 100n; C_0402_1005Metric; LCSC C1525
C63, C68: 100u; C_1206_3216Metric; LCSC C15008
D6: SMCJ30A; D_SMC; LCSC C224048
D7: SS34; D_SMA; LCSC C8678
D8, D10: B5819W; D_SOD-123; LCSC C8598
D9: B360A; D_SMA; LCSC C94193
D12: SMAJ33A; D_SMA; LCSC C223988
D38, D39: BAT54WS; D_SOD-323; LCSC C124205
F1: BSMD1812-110-33V; Fuse_1812_4532Metric; LCSC C883150
L1: 2.2uH; L_Sunlord_MWSA0503S; LCSC C177247
L2: 10uH; L_Sunlord_MWSA0603S; LCSC C132141
Q20: BCP53-16; SOT-223; LCSC C85085
R7: 1; R_0603_1608Metric; LCSC C22936
R8: 10k; R_0603_1608Metric; LCSC C25804
R9: 68k; R_0603_1608Metric; LCSC C23231
R10, R143: 12k; R_0603_1608Metric; LCSC C22790
R11, R13: 33k; R_0402_1005Metric; LCSC C25779
R12, R14: 6.8k; R_0402_1005Metric; LCSC C25917
R141: 1k; R_0603_1608Metric; LCSC C21190
R142: 5.1k; R_0603_1608Metric; LCSC C23186
U2: LMR14020; SOIC-8-1EP_3.9x4.9mm_P1.27mm_EP2.29x3mm; LCSC C187824
U3, U14: TLS115B0EJ; Infineon_PG-DSO-8-27_3.9x4.9mm_EP2.65x3mm; LCSC C3743696
U4: LDL1117S33R; SOT-223-3_TabPin2; LCSC C435835
U15: TL431AIDBZR; SOT-23; LCSC C23892

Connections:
+3V3: C27.1, C63.1, C68.1, D38.1 (K), D39.1 (K), Q20.3 (E), R141.1, R142.1, U4.2 (VO); also elsewhere on the board
+5V: C21.1, C22.1, C23.1, C26.1, C59.1, D10.1 (K), L2.2, R9.1, U3.5 (ADJ), U4.3 (VI), U14.5 (ADJ); also elsewhere on the board
+12V: C24.1, C62.1, D12.1 (K), F1.2, L1.1, R7.1, U3.7 (EN), U3.8 (I), U14.7 (EN), U14.8 (I)
/Power/+12V_F: C17.1, C18.1, C71.1, L1.2, U2.2 (VIN), U2.3 (EN)
/Power/+12V_IN: D7.1 (K), D8.1 (K), F1.1
/Power/BUCK_BOOT: C19.1, U2.1 (BOOT)
/Power/BUCK_FB: C21.2, R9.2, R10.1, U2.5 (FB)
/Power/BUCK_RT: R8.1, U2.4 (RT/SYNC)
/Power/BUCK_SS: C20.1, U2.6 (SS)
/Power/BUCK_SW: C19.2, D9.1 (K), L2.1, U2.8 (SW)
/Power/DAMP: C16.1, R7.2
/Power/SH_K: Q20.1 (B), R141.2, U15.1 (K)
/Power/SH_REF: R142.2, R143.1, U15.2 (REF)
AN_VBATT: C28.1, D38.2 (A), R11.2, R12.1; also elsewhere on the board
AN_VIGN: C29.1, D39.2 (A), R13.2, R14.1; also elsewhere on the board
GND: C16.2, C17.2, C18.2, C20.2, C22.2, C23.2, C24.2, C25.2, C26.2, C27.2, C28.2, C29.2, C59.2, C61.2, C62.2, C63.2, C68.2, C71.2, D6.2 (A), D9.2 (A), D12.2 (A), Q20.2 (C), Q20.4 (C), R8.2, R10.2, R12.2, R14.2, R143.2, U2.7 (GND), U2.9 (EP), U3.3 (GND), U3.9 (EP), U4.1 (GND), U14.3 (GND), U14.9 (EP), U15.3 (A); also elsewhere on the board
USB_VBUS: D10.2 (A); also elsewhere on the board
V5_EXT: C61.1, U14.1 (Q); also elsewhere on the board
V5_SENS: C25.1, U3.1 (Q); also elsewhere on the board
VBAT_IN: D6.1 (K), D7.2 (A), R11.1; also elsewhere on the board
VIGN_IN: D8.2 (A), R13.1; also elsewhere on the board

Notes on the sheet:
Input protection (fused, TVS-clamped logic supply) and 5 V buck (LMR14020, 5 V / 2 A)
USB VBUS powers the logic on the bench
Fsw ~ 1 MHz (RT 10k); Vout = 0.75 V x (1 + 68k/12k) = 5.0 V
3.3 V LDO
Protected 5 V sensor supply (TLS115 tracks +5V)
Harness sensor 5 V (V5_EXT, second TLS115; J1-13 to the harness and AUX header)
+3V3 shunt clamp: TL431 senses 3.56 V (5.1k / 12k) and turns on a PNP to ground
Battery / ignition sense (divide by 5.85)

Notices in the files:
daughterboard/README.md:
- **On-board wideband controller.** The complete FOME / rusEFI open-source wideband controller (MIT licence, github.com/mck1117/wideband, `board_module` rev C) is now on this board.
y` (parts + netlist), `placement.py`, `build_pcb.py`, `route.py`, `wideband.py` (the wideband circuit, mapped from the FOME module in `wideband_ref/` under its MIT licence), `wb_clean.py` (its rev 0.3 placement and heater copper; `wb_preview.py` draws a placement preview), `wb_build.py` (the rev 0.2
